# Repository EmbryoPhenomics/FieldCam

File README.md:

# FieldCam

## A submersible field camera and sensor instrument

FieldCam is a versatile, waterproof imaging and sensing instrument, powered by consumer AA batteries and capable of long term timelapse imaging out in the field.

 Some of the key specifications of this instrument are as follows:

| Component | Description |
|:---|:---|
| Waterproof enclosure | Acrylic tube with aluminium end caps rated to 130m depth |
| Battery | 17.1 Ah AA battery pack (~24 hrs continuous video recording). Capacity for additional 22.8 Ah AA battery pack (~30 hrs). Low power mode is > 10 years with continuous system and sensor monitoring (5 second resolution) |
| Processors | STM32 L4 microcontroller for system control and low power standby. Raspberry Pi Zero 2W for video and image capture, 32gb and 1Tb SD cards for storage respectively |
| Camera sensor | CMOS 12-megapixel (Sony IMX708) |
| Video resolution | 1080p50fps maximum. Resolution and framerate can be configured using built-in app |
| Focus | Phase Detection Autofocus (PDAF) or manual adjustable focus. Range 5cm to > 2m. | 
| Camera parameters | Exposure (Auto or manual), analogue gain and auto-white balance modes can all be configured via Web App |
| Lighting | Built-in adjustable LEDs (x2) with up to 170 lm each |
| Sensors | Temperature and light built-in. Pressure, salinity, pH and O2 available with additional sensor pack | 
| Configuration | Setup via Web App using smartphone or laptop, connected to the instrument’s wifi hotspot. Web App enables live streaming and config of camera sensor, viewing of system status and programming of experimental schedule.  All data, including video and sensor logs can be downloaded via network file sharing when in setup mode | 
| Dimensions | 70 mm x 195 mm |

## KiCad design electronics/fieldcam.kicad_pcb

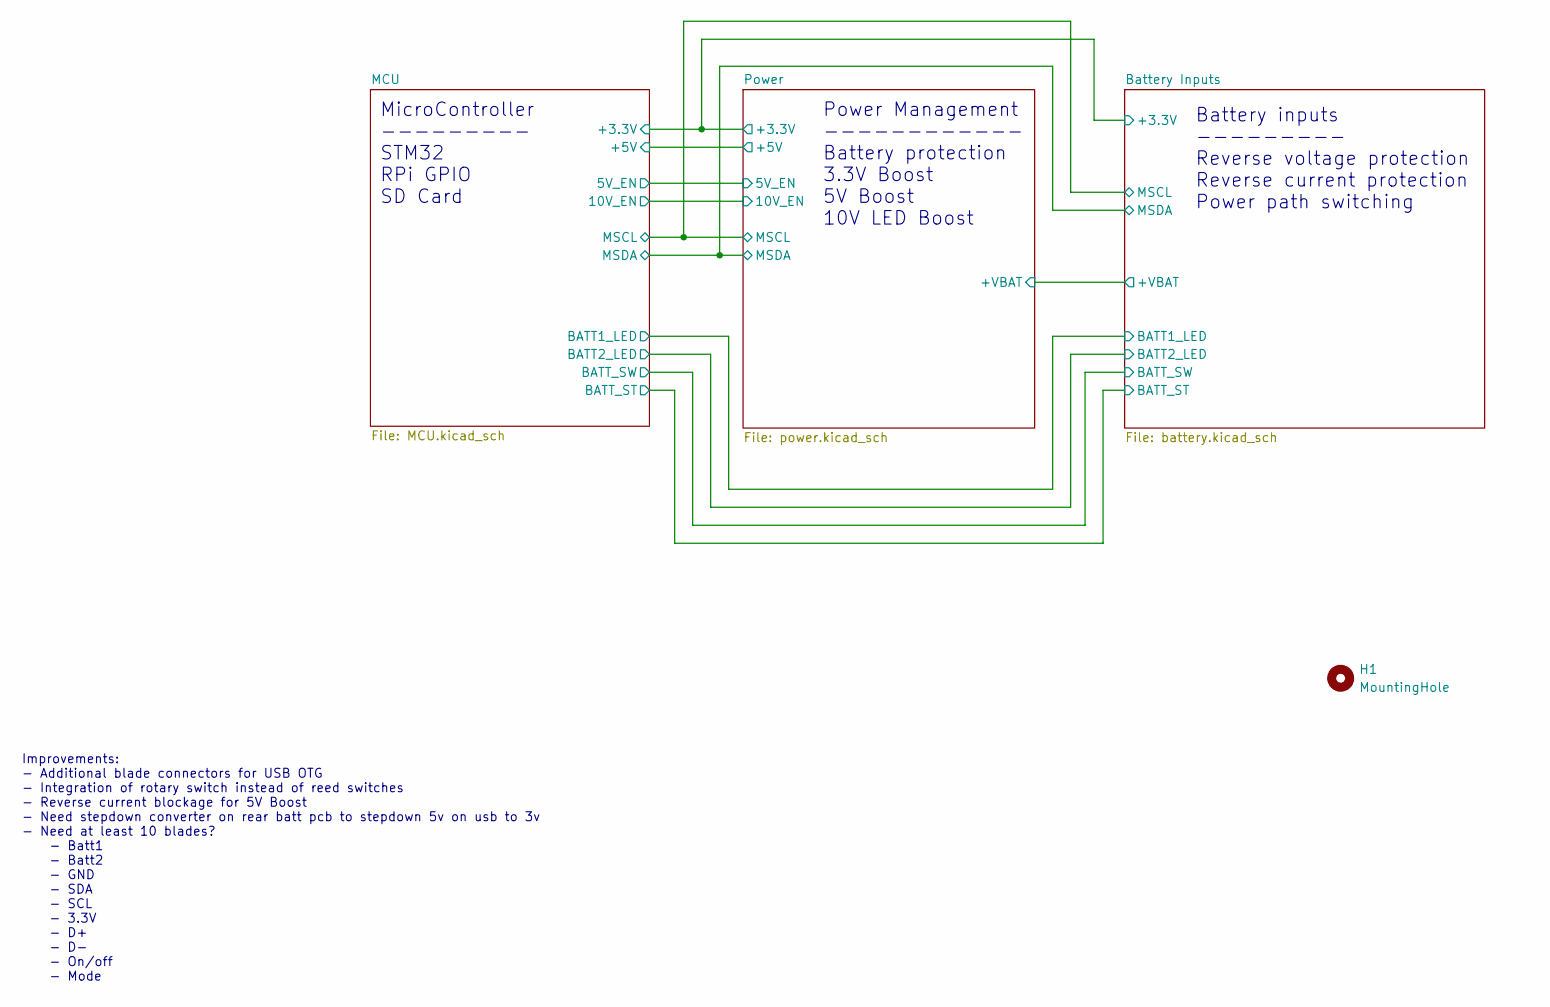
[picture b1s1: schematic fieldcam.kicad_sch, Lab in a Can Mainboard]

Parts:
H1: MountingHole; MountingHole_2.7mm_M2.5

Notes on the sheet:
Improvements: - Additional blade connectors for USB OTG - Integration of rotary switch instead of reed switches - Reverse current blockage for 5V Boost - Need stepdown converter on rear batt pcb to stepdown 5v on usb to 3v - Need at least 10 blades? - Batt1 - Batt2 - GND - SDA - SCL - 3.3V - D+ - D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
Power Management ------------ Battery protection 3.3V Boost 5V Boost 10V LED Boost
Battery inputs --------- Reverse voltage protection Reverse current protection Power path switching
MicroController --------- STM32 RPi GPIO SD Card

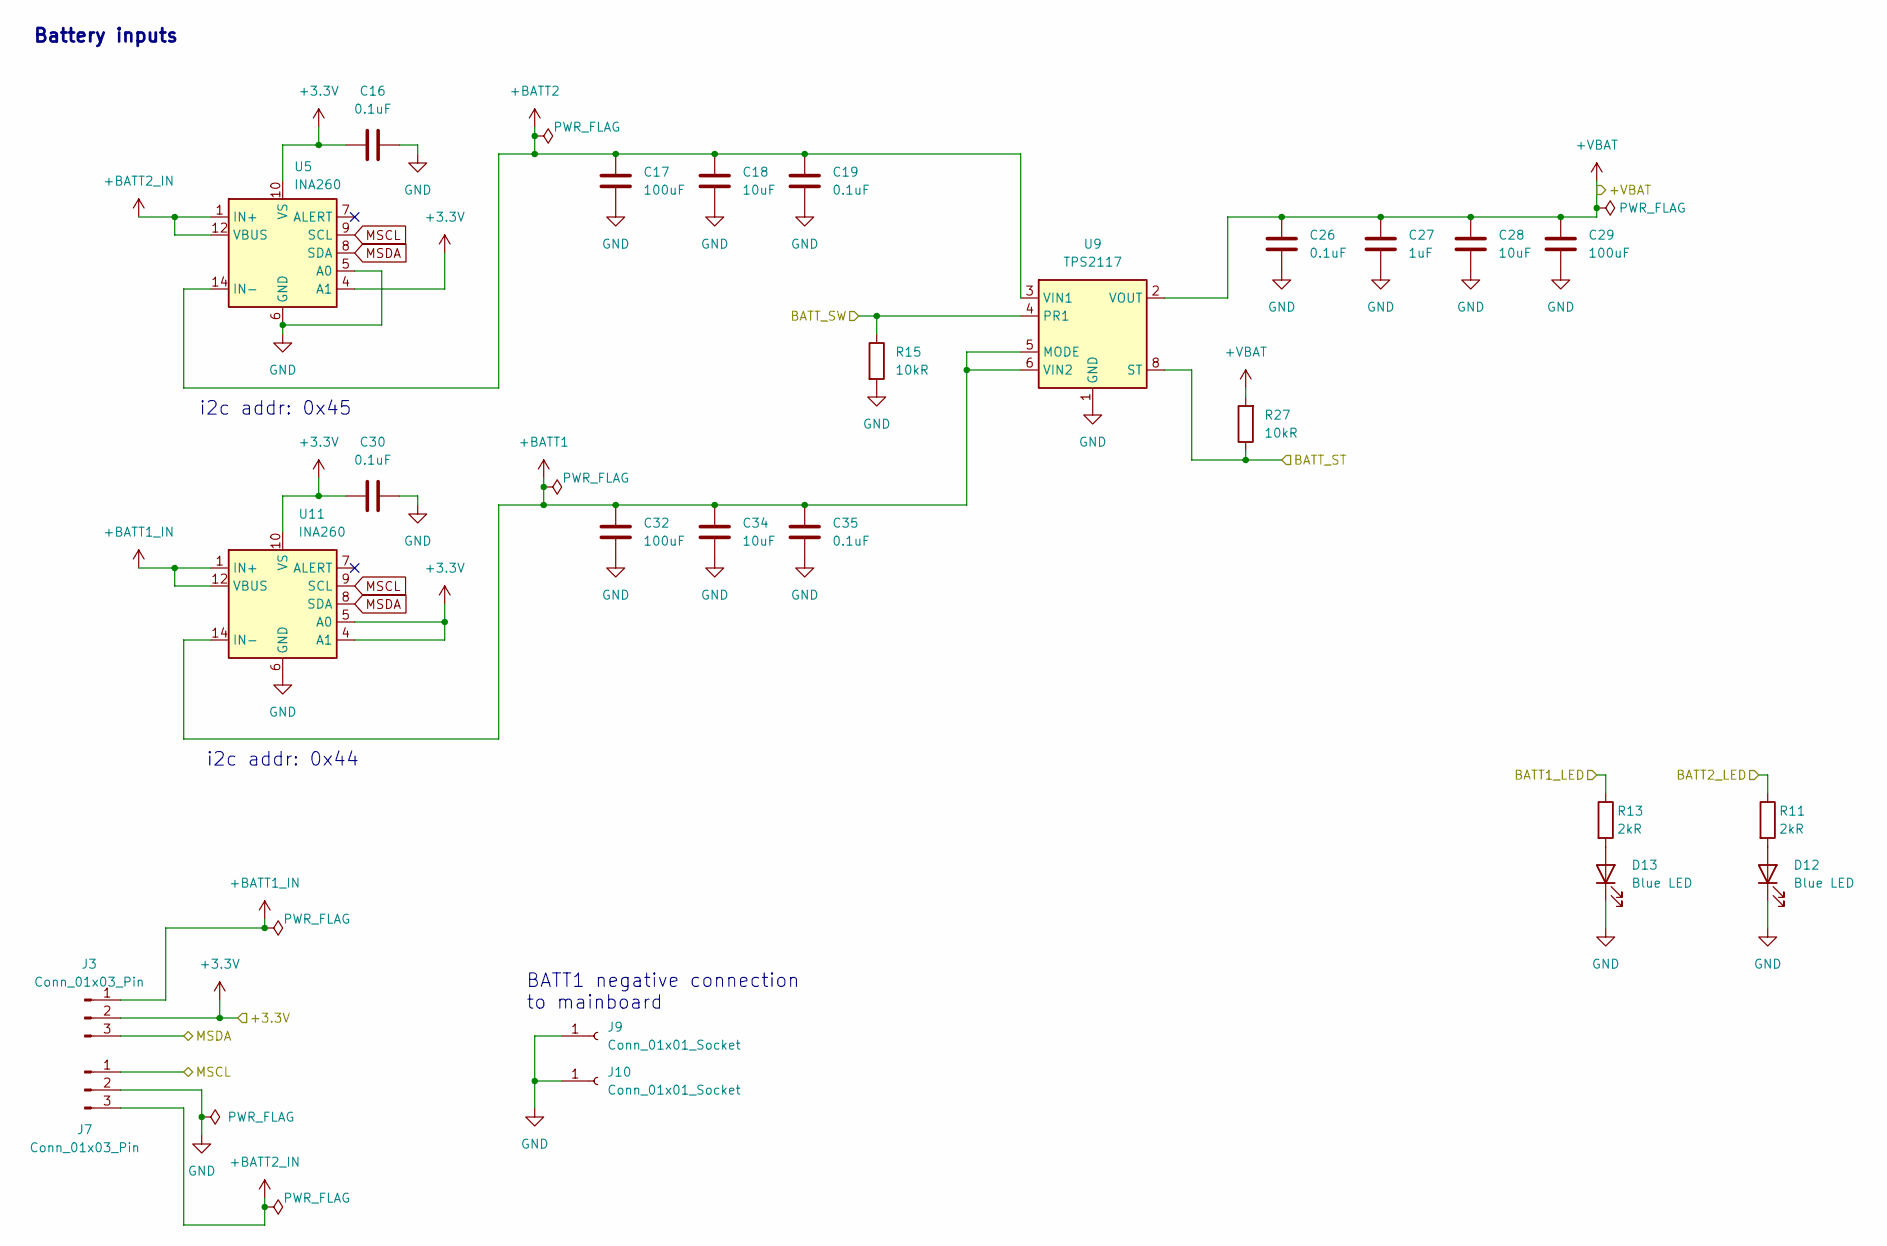
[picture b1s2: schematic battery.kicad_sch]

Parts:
C16, C19, C26, C30, C35: 0.1uF; C_0603_1608Metric
C17, C29, C32: 100uF; C_1210_3225Metric
C18, C28, C34: 10uF; C_0805_2012Metric
C27: 1uF; C_0603_1608Metric
D12, D13: Blue LED; LED_0603_1608Metric
J3, J7: Conn_01x03_Pin; 16129011
J9, J10: Conn_01x01_Socket; TestPoint_Pad_2.0x2.0mm
R11, R13: 2kR; R_0603_1608Metric
R15, R27: 10kR; R_0603_1608Metric
U5, U11: INA260; TSSOP-16_4.4x5mm_P0.65mm
U9: TPS2117; SOT-583-8

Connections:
+3.3V: C16.1, C30.1, J3.2, U5.4 (A1), U5.10 (VS), U11.4 (A1), U11.5 (A0), U11.10 (VS); also elsewhere on the board
+BATT1: C32.1, C34.1, C35.1, U9.5 (MODE), U9.6 (VIN2), U11.14 (IN-), U11.15 (IN-), U11.16 (IN-)
+BATT1_IN: J3.1, U11.1 (IN+), U11.2 (IN+), U11.3 (IN+), U11.12 (VBUS)
+BATT2: C17.1, C18.1, C19.1, U5.14 (IN-), U5.15 (IN-), U5.16 (IN-), U9.3 (VIN1)
+BATT2_IN: J7.3, U5.1 (IN+), U5.2 (IN+), U5.3 (IN+), U5.12 (VBUS)
+VBAT: C26.1, C27.1, C28.1, C29.1, R27.2, U9.2 (VOUT), U9.7 (VOUT); also elsewhere on the board
/Battery Inputs/BATT1_LED: R13.1; also elsewhere on the board
/Battery Inputs/BATT2_LED: R11.1; also elsewhere on the board
/Battery Inputs/BATT_ST: R27.1, U9.8 (ST); also elsewhere on the board
/Battery Inputs/BATT_SW: R15.1, U9.4 (PR1); also elsewhere on the board
GND: C16.2, C17.2, C18.2, C19.2, C26.2, C27.2, C28.2, C29.2, C30.2, C32.2, C34.2, C35.2, D12.1 (K), D13.1 (K), J7.2, J9.1 (Pin_1_1), J10.1 (Pin_1_1), R15.2, U5.5 (A0), U5.6 (GND), U5.11 (GND), U9.1 (GND), U11.6 (GND), U11.11 (GND); also elsewhere on the board
MSCL: J7.1, U5.9 (SCL), U11.9 (SCL); also elsewhere on the board
MSDA: J3.3, U5.8 (SDA), U11.8 (SDA); also elsewhere on the board
unnamed: D12.2 (A), R11.2
unnamed: D13.2 (A), R13.2

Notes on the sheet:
i2c addr: 0x45
BATT1 negative connection to mainboard
Battery inputs
i2c addr: 0x44

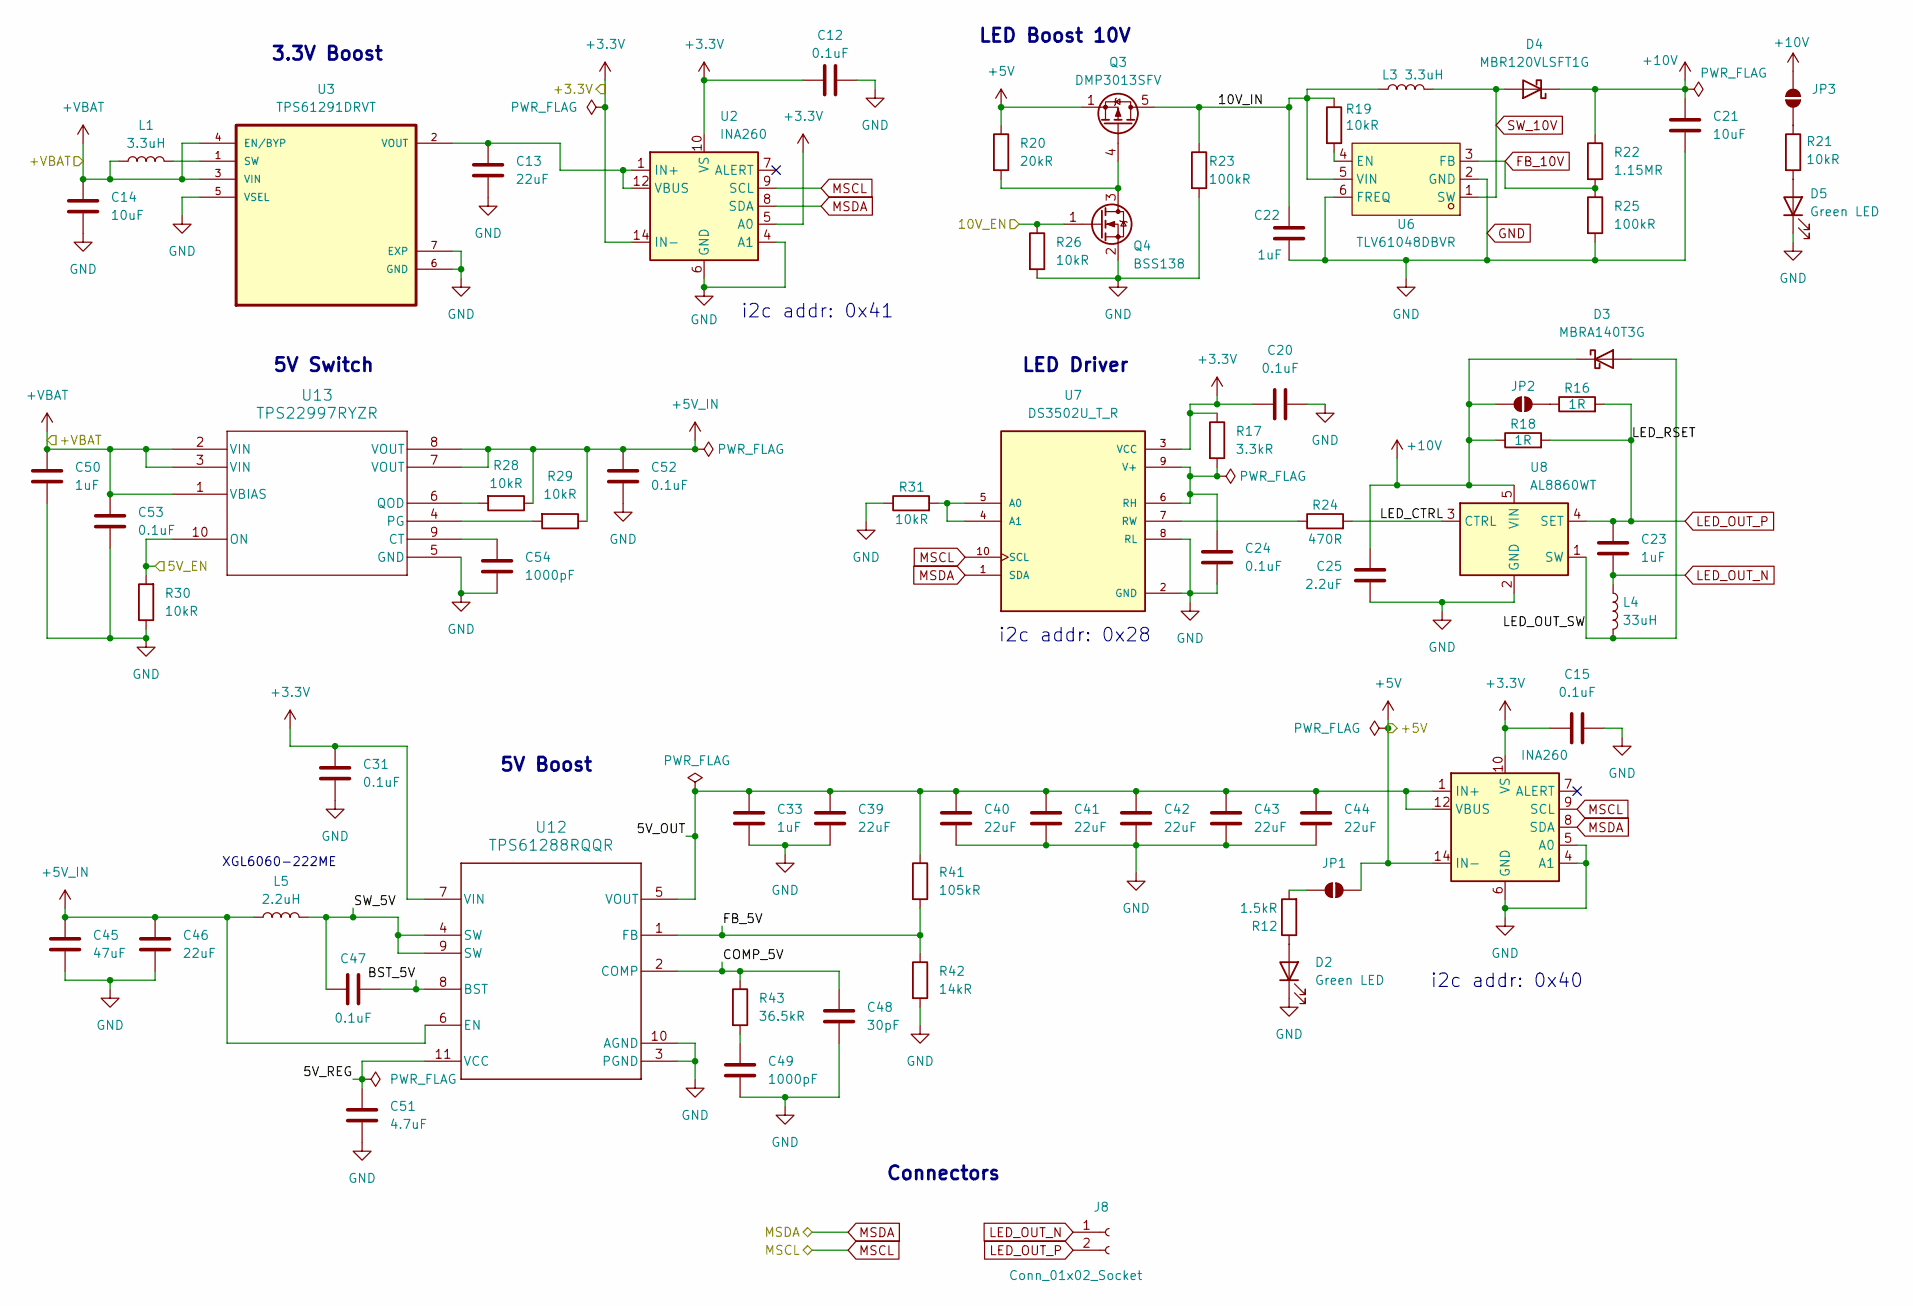
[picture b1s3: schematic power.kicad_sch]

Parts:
C12, C15, C20, C24, C47, C52, C53: 0.1uF; C_0603_1608Metric
C13: 22uF; C_0805_2012Metric
C14, C21: 10uF; C_0805_2012Metric
C22, C33: 1uF; C_0603_1608Metric
C23, C50: 1uF; C_0805_2012Metric
C25: 2.2uF; C_0805_2012Metric
C31: 0.1uF; C_0402_1005Metric
C39, C40, C41, C42, C43, C44, C46: 22uF; C_1206_3216Metric
C45: 47uF; C_1206_3216Metric
C48: 30pF; C_0402_1005Metric
C49, C54: 1000pF; C_0402_1005Metric
C51: 4.7uF; C_0603_1608Metric
D2, D5: Green LED; LED_0603_1608Metric
D3: MBRA140T3G; SMA_L4.3-W2.6-LS5.2-RD
D4: MBR120VLSFT1G
J8: Conn_01x02_Socket; JST_PH_S2B-PH-K_1x02_P2.00mm_Horizontal
JP1, JP2, JP3: SolderJumper_2_Open; SolderJumper-2_P1.3mm_Open_Pad1.0x1.5mm
L1, L3: 3.3uH; L_Coilcraft_XAL4030-XXX
L4: 33uH; L_Bourns_SRP7028A_7.3x6.6mm
L5: 2.2uH; L_Coilcraft_XAL6060-XXX
Q3: DMP3013SFV; Diodes_PowerDI3333-8
Q4: BSS138; SOT-23
R12: 1.5kR; R_0603_1608Metric
R16, R18: 1R; R_1206_3216Metric
R17: 3.3kR; R_0603_1608Metric
R19, R21, R26, R28, R29, R30, R31: 10kR; R_0603_1608Metric
R20: 20kR; R_0603_1608Metric
R22: 1.15MR; R_0603_1608Metric
R23, R25: 100kR; R_0603_1608Metric
R24: 470R; R_0603_1608Metric
R41: 105kR; R_0402_1005Metric
R42: 14kR; R_0402_1005Metric
R43: 36.5kR; R_0402_1005Metric
U2, U4: INA260; TSSOP-16_4.4x5mm_P0.65mm
U3: TPS61291DRVT; TPS61291
U6: TLV61048DBVR; SOT-23-6_L2.9-W1.6-P0.95-LS2.8-BR; LCSC Part C2861467
U7: DS3502U_T_R; SOP50P490X110-10N; PARTREV 23/05/19
U8: AL8860WT; TSOT-23-5
U12: TPS61288RQQR; TPS61288_VQFN-HR-11_L3.0-W2.5-P0.50-TL
U13: TPS22997RYZR; WQFN-HR10_RYZ_TEX

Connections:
+3.3V: C12.1, C15.1, C20.1, C31.1, R17.1, U2.5 (A0), U2.10 (VS), U2.14 (IN-), U2.15 (IN-), U2.16 (IN-), U4.10 (VS), U7.3 (VCC), U12.7 (VIN); also elsewhere on the board
+5V: JP1.1 (A), Q3.1 (S), Q3.2 (S), Q3.3 (S), R20.1, U4.14 (IN-), U4.15 (IN-), U4.16 (IN-); also elsewhere on the board
+5V_IN: C45.1, C46.1, C52.1, L5.1, R28.1, R29.1, U12.6 (EN), U13.7 (VOUT), U13.8 (VOUT)
+10V: C21.1, C25.1, D3.1 (K), D4.1 (K), JP2.2 (B), JP3.2 (B), R18.1, R22.1, U8.5 (VIN)
+VBAT: C14.1, C50.1, C53.1, L1.1, U3.3 (VIN), U3.4 (EN/BYP), U13.1 (VBIAS), U13.2 (VIN), U13.3 (VIN); also elsewhere on the board
/MCU/5V_EN: R30.2, U13.10 (ON); also elsewhere on the board
/MCU/10V_EN: Q4.1 (G), R26.1; also elsewhere on the board
/Power/5V_OUT: C33.1, C39.1, C40.1, C41.1, C42.1, C43.1, C44.1, R41.1, U4.1 (IN+), U4.2 (IN+), U4.3 (IN+), U4.12 (VBUS), U12.5 (VOUT)
/Power/5V_REG: C51.1, U12.11 (VCC)
/Power/10V_IN: C22.1, L3.1, Q3.5 (D), R19.1, R23.1, U6.5 (VIN)
/Power/BST_5V: C47.2, U12.8 (BST)
/Power/COMP_5V: C48.1, R43.1, U12.2 (COMP)
/Power/FB_5V: R41.2, R42.1, U12.1 (FB)
/Power/LED_CTRL: R24.2, U8.3 (CTRL)
/Power/LED_OUT_SW: D3.2 (A), L4.2, U8.1 (SW)
/Power/SW_5V: C47.1, L5.2, U12.4 (SW), U12.9 (SW)
FB_10V: R22.2, R25.1, U6.3 (FB)
GND: C12.2, C13.2, C14.2, C15.2, C20.2, C21.2, C22.2, C24.1, C25.2, C31.2, C33.2, C39.2, C40.2, C41.2, C42.2, C43.2, C44.2, C45.2, C46.2, C48.2, C49.2, C50.2, C51.2, C52.2, C53.2, C54.2, D2.1 (K), D5.1 (K), Q4.2 (S), R23.2, R25.2, R26.2, R30.1, R31.1, R42.2, U2.4 (A1), U2.6 (GND), U2.11 (GND), U3.5 (VSEL), U3.6 (GND), U3.7 (EXP), U4.4 (A1), U4.5 (A0), U4.6 (GND), U4.11 (GND), U6.2 (GND), U6.6 (FREQ), U7.2 (GND), U7.8 (RL), U8.2 (GND), U12.3 (PGND), U12.10 (AGND), U13.5 (GND); also elsewhere on the board
LED_OUT_N: C23.2, J8.1, L4.1
LED_OUT_P: C23.1, J8.2, R16.2, R18.2, U8.4 (SET)
MSCL: U2.9 (SCL), U4.9 (SCL), U7.10 (SCL); also elsewhere on the board
MSDA: U2.8 (SDA), U4.8 (SDA), U7.1 (SDA); also elsewhere on the board
unnamed: C49.1, R43.2
unnamed: D2.2 (A), R12.1
unnamed: D5.2 (A), R21.2
unnamed: JP1.2 (B), R12.2
unnamed: JP2.1 (A), R16.1
unnamed: JP3.1 (A), R21.1
unnamed: Q3.4 (G), Q4.3 (D), R20.2
unnamed: C13.1, U2.1 (IN+), U2.2 (IN+), U2.3 (IN+), U2.12 (VBUS), U3.2 (VOUT)
unnamed: L1.2, U3.1 (SW)
unnamed: R19.2, U6.4 (EN)
unnamed: R31.2, U7.4 (A1), U7.5 (A0)
unnamed: C24.2, R17.2, U7.6 (RH), U7.9 (V+)
unnamed: R24.1, U7.7 (RW)
unnamed: C54.1, U13.9 (CT)
unnamed: R29.2, U13.4 (PG)
unnamed: R28.2, U13.6 (QOD)
SW_10V: D4.2 (A), L3.2, U6.1 (SW)

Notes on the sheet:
5V Switch
i2c addr: 0x28
i2c addr: 0x41
LED Driver
LED Boost 10V
i2c addr: 0x40
XGL6060-222ME
Connectors
3.3V Boost
5V Boost

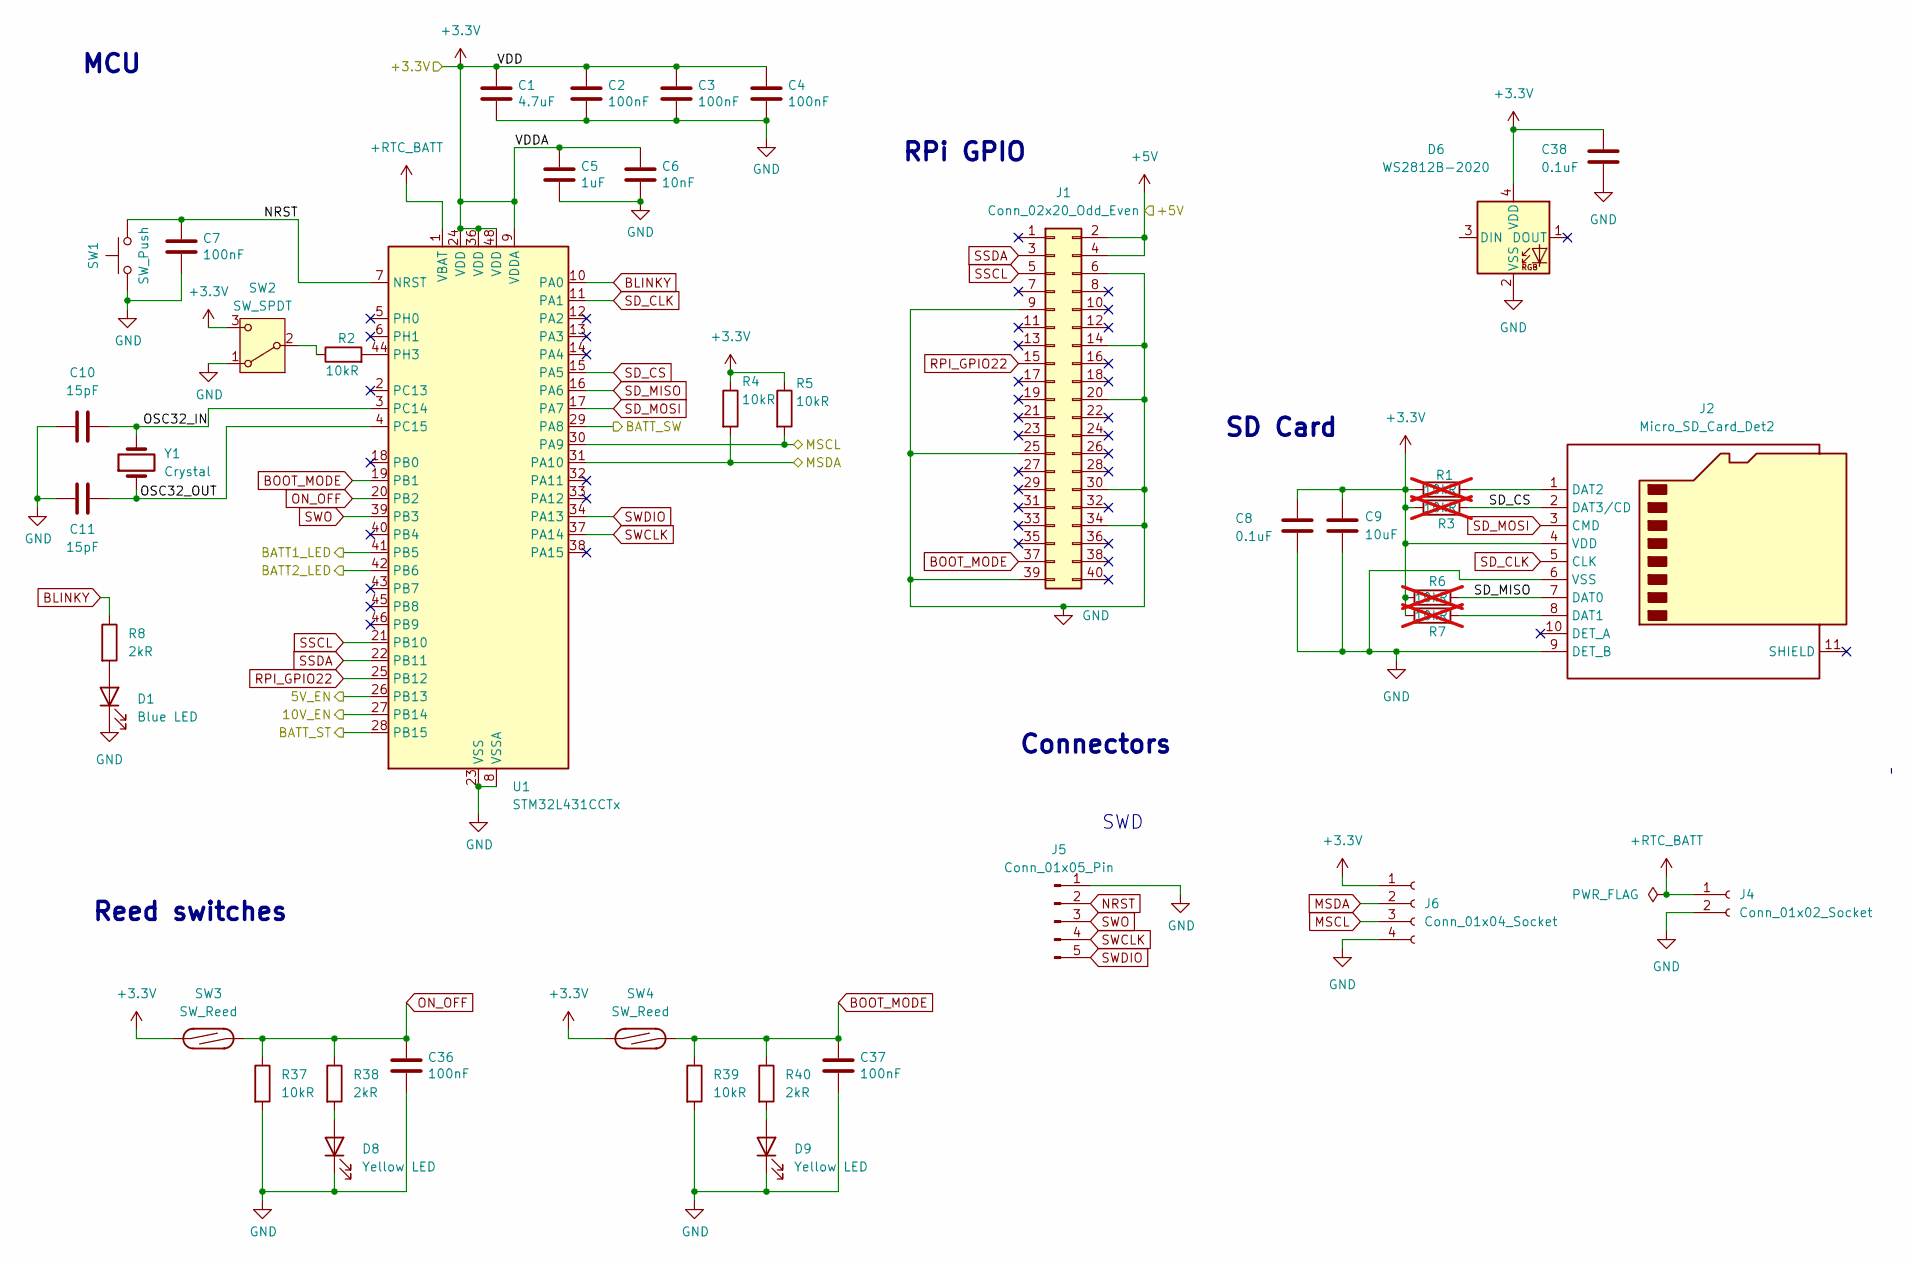
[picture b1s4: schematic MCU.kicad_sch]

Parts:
C1: 4.7uF; C_0603_1608Metric
C2, C3, C4, C7, C36, C37: 100nF; C_0402_1005Metric
C5: 1uF; C_0603_1608Metric
C6: 10nF; C_0402_1005Metric
C8, C38: 0.1uF; C_0402_1005Metric
C9: 10uF; C_0603_1608Metric
C10, C11: 15pF; C_0402_1005Metric
D1: Blue LED; LED_0603_1608Metric
D6: WS2812B-2020; LED_WS2812B-2020_PLCC4_2.0x2.0mm
D8, D9: Yellow LED; LED_0603_1608Metric
J1: Conn_02x20_Odd_Even; CONN-SMD_FH-00369_2x40
J2: Micro_SD_Card_Det2; microSD_HC_Molex_104031-0811
J4: Conn_01x02_Socket; JST_SH_SM02B-SRSS-TB_1x02-1MP_P1.00mm_Horizontal
J5: Conn_01x05_Pin; JST_SH_BM05B-SRSS-TB_1x05-1MP_P1.00mm_Vertical
J6: Conn_01x04_Socket; JST_SH_SM04B-SRSS-TB_1x04-1MP_P1.00mm_Horizontal
R1, R3, R6, R7: 10kR; R_0402_1005Metric; not fitted
R2, R4, R5: 10kR; R_0402_1005Metric
R8, R38, R40: 2kR; R_0603_1608Metric
R37, R39: 10kR; R_0603_1608Metric
SW1: SW_Push; SW-SMD_L3.9-W3.0-P4.45
SW2: SW_SPDT; SW-SMD_MSK12CO2
SW3, SW4: SW_Reed; SENSOR-SMD_59170-1-S-00-D
U1: STM32L431CCTx; LQFP-48_7x7mm_P0.5mm
Y1: Crystal; FC-135R_L3.2-W1.5

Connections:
+3.3V: C1.1, C2.1, C3.1, C4.1, C5.1, C6.1, C8.1, C9.1, C38.1, D6.4 (VDD), J2.4 (VDD), J6.1, R1.1, R3.1, R4.1, R5.1, R6.1, R7.1, SW2.3 (C), SW3.1, SW4.1, U1.9 (VDDA), U1.24 (VDD), U1.36 (VDD), U1.48 (VDD); also elsewhere on the board
+5V: J1.2, J1.4; also elsewhere on the board
+RTC_BATT: J4.1, U1.1 (VBAT)
/Battery Inputs/BATT1_LED: U1.41 (PB5); also elsewhere on the board
/Battery Inputs/BATT2_LED: U1.42 (PB6); also elsewhere on the board
/Battery Inputs/BATT_ST: U1.28 (PB15); also elsewhere on the board
/Battery Inputs/BATT_SW: U1.29 (PA8); also elsewhere on the board
/MCU/5V_EN: U1.26 (PB13); also elsewhere on the board
/MCU/10V_EN: U1.27 (PB14); also elsewhere on the board
/MCU/OSC32_IN: C10.2, U1.3 (PC14), Y1.2
/MCU/OSC32_OUT: C11.2, U1.4 (PC15), Y1.1
BLINKY: R8.1, U1.10 (PA0)
BOOT_MODE: C37.1, J1.37, R39.1, R40.1, SW4.2, U1.19 (PB1)
GND: C1.2, C2.2, C3.2, C4.2, C5.2, C6.2, C7.2, C8.2, C9.2, C10.1, C11.1, C36.2, C37.2, C38.2, D1.1 (K), D6.2 (VSS), D8.1 (K), D9.1 (K), J1.6, J1.9, J1.14, J1.20, J1.25, J1.30, J1.34, J1.39, J2.6 (VSS), J2.9 (DET_B), J4.2, J5.1, J6.4, R37.2, R39.2, SW1.1, SW2.1 (A), U1.8 (VSSA), U1.23 (VSS), U1.35 (VSS), U1.47 (VSS); also elsewhere on the board
MSCL: J6.3, R5.2, U1.30 (PA9); also elsewhere on the board
MSDA: J6.2, R4.2, U1.31 (PA10); also elsewhere on the board
NRST: C7.1, J5.2, SW1.2, U1.7 (NRST)
unnamed: D1.2 (A), R8.2
unnamed: D8.2 (A), R38.2
unnamed: D9.2 (A), R40.2
unnamed: J2.8 (DAT1), R7.2
unnamed: J2.1 (DAT2), R1.2
unnamed: R2.1, SW2.2 (B)
unnamed: R2.2, U1.44 (PH3)
ON_OFF: C36.1, R37.1, R38.1, SW3.2, U1.20 (PB2)
RPI_GPIO22: J1.15, U1.25 (PB12)
SD_CLK: J2.5 (CLK), U1.11 (PA1)
SD_CS: J2.2 (DAT3/CD), R3.2, U1.15 (PA5)
SD_MISO: J2.7 (DAT0), R6.2, U1.16 (PA6)
SD_MOSI: J2.3 (CMD), U1.17 (PA7)
SSCL: J1.5, U1.21 (PB10)
SSDA: J1.3, U1.22 (PB11)
SWCLK: J5.4, U1.37 (PA14)
SWDIO: J5.5, U1.34 (PA13)
SWO: J5.3, U1.39 (PB3)

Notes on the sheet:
Connectors
SWD
MCU
RPi GPIO
Reed switches
SD Card

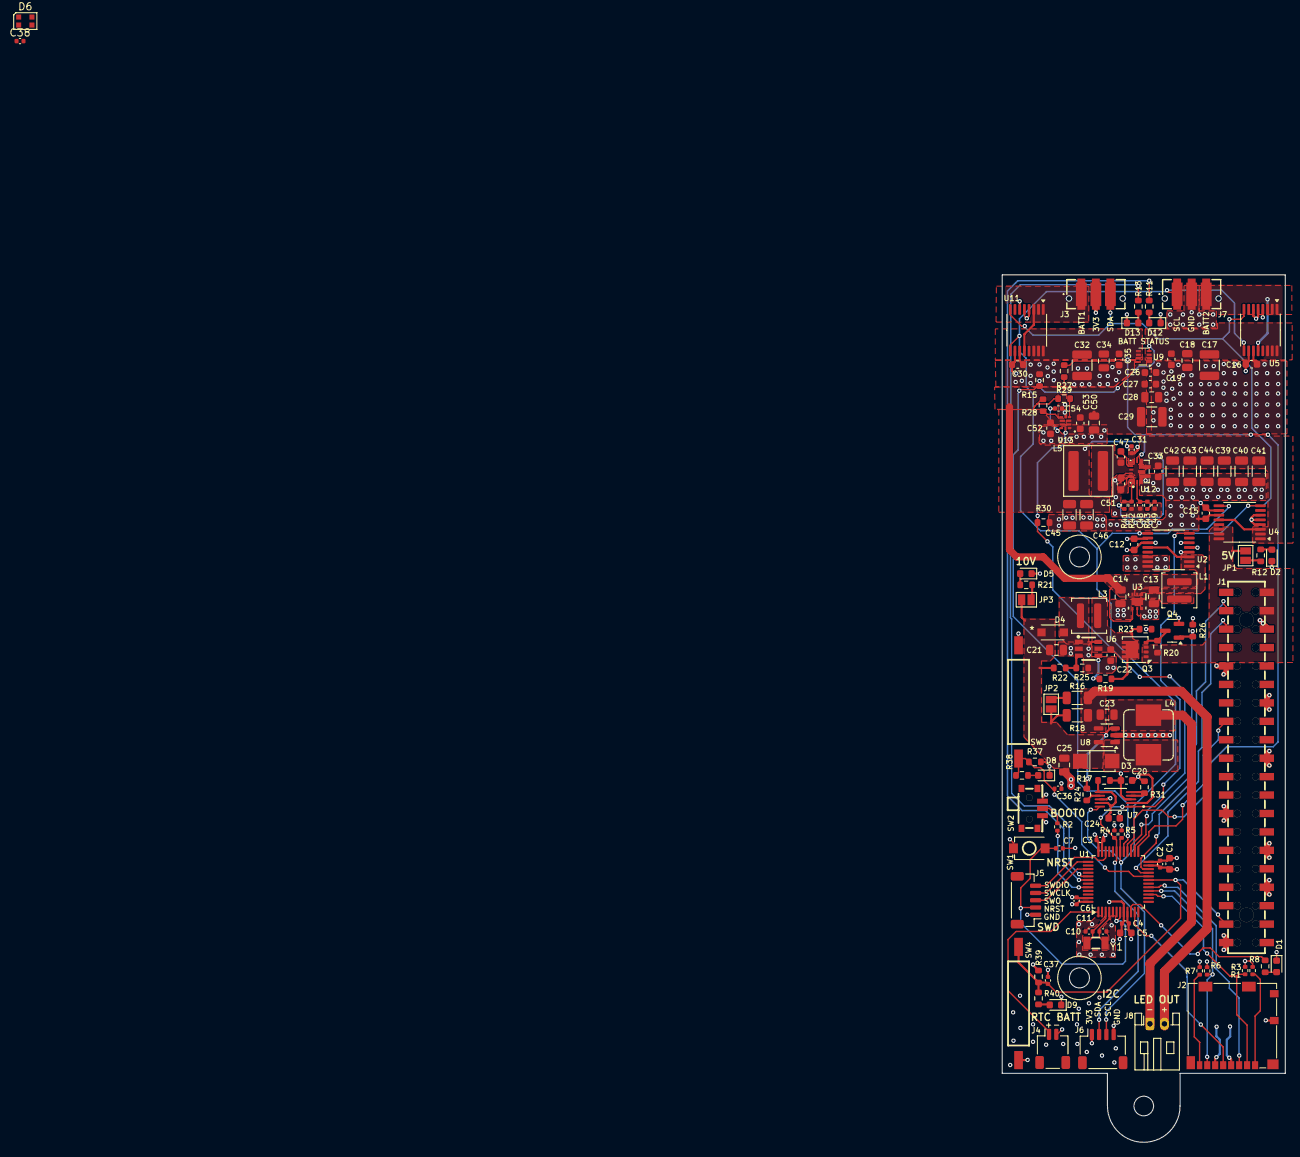
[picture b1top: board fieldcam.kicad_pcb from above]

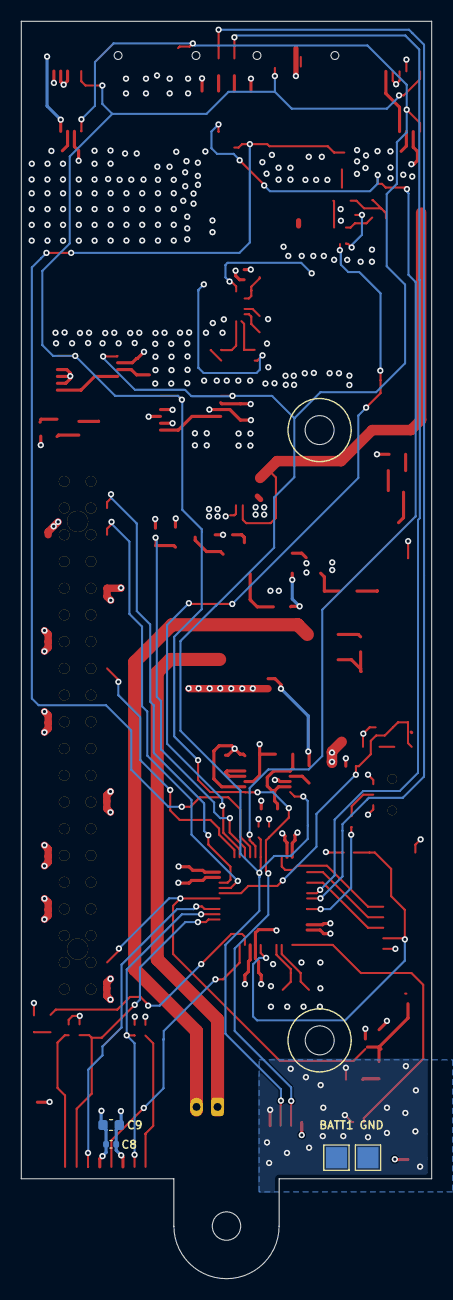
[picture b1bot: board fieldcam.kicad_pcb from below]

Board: 4 copper layers, 39.0 x 119.5 mm, 136 parts (4 on the bottom side), 73 nets.

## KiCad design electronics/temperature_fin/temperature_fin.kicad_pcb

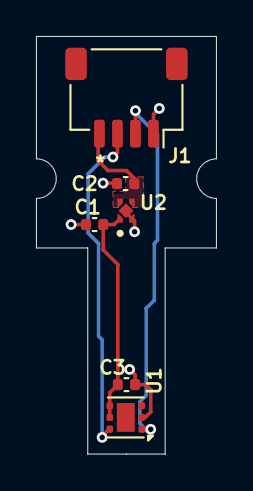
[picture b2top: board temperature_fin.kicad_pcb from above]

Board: 2 copper layers, 10.0 x 23.2 mm, 6 parts (0 on the bottom side), 5 nets.

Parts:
C1, C2: 1uF; C_0402_1005Metric
C3: 0.1uF; C_0402_1005Metric
J1: Conn_01x04_Socket; JST_SH_SM04B-SRSS-TB_1x04-1MP_P1.00mm_Horizontal
U1: TMP117xxDRV; WSON-6-1EP_2x2mm_P0.65mm_EP1x1.6mm
U2: TPS7A0228PDQNR; IC_TPS7A0228PDQNR

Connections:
+2V8: C1.1, C3.1, U1.4 (ADD0), U1.5 (V+), U2.1 (OUT)
+3V3: C2.1, J1.4, U2.3 (EN), U2.4 (IN)
GND: C1.2, C2.2, C3.2, J1.1, U1.2 (GND), U2.2 (GND), U2.5 (THERMAL_PAD)
SCL: J1.2, U1.1 (SCL)
SDA: J1.3, U1.6 (SDA)

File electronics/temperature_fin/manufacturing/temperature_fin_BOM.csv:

"Reference","Qty","Value","DNP","Exclude from BOM","Exclude from Board","Footprint","Datasheet"
"C1,C2","2","1uF","","","","Capacitor_SMD:C_0402_1005Metric","~"
"C3","1","0.1uF","","","","Capacitor_SMD:C_0402_1005Metric","~"
"J1","1","Conn_01x04_Socket","","","","Connector_JST:JST_SH_SM04B-SRSS-TB_1x04-1MP_P1.00mm_Horizontal","~"
"U1","1","TMP117xxDRV","","","","Package_SON:WSON-6-1EP_2x2mm_P0.65mm_EP1x1.6mm","https://www.ti.com/lit/ds/symlink/tmp117.pdf"
"U2","1","TPS7A0228PDQNR","","","","jlcpcb:IC_TPS7A0228PDQNR",""

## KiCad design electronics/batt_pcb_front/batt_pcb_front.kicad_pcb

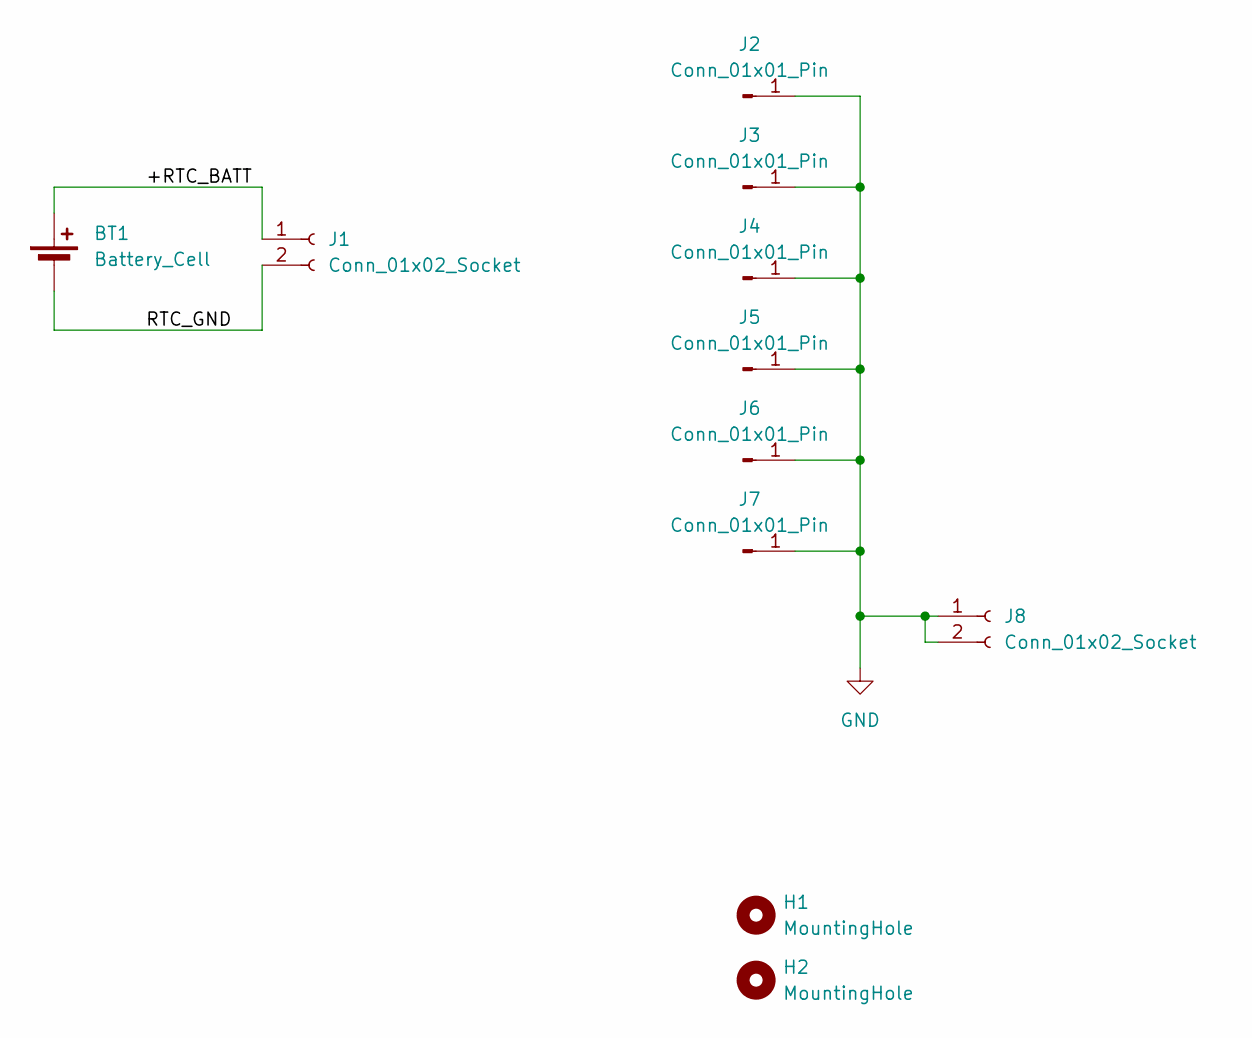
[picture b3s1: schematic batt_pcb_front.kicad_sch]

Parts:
BT1: Battery_Cell; BatteryHolder_Keystone_3000_1x12mm
H1, H2: MountingHole; MountingHole_2.7mm_M2.5
J1: Conn_01x02_Socket; JST_SH_BM02B-SRSS-TB_1x02-1MP_P1.00mm_Vertical
J2, J3, J4, J5, J6, J7: Conn_01x01_Pin; TestPoint_Pad_D4.0mm
J8: Conn_01x02_Socket; JST_PH_S2B-PH-SM4-TB_1x02-1MP_P2.00mm_Horizontal

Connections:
/+RTC_BATT: BT1.1 (+), J1.1
/RTC_GND: BT1.2 (-), J1.2
GND: J2.1, J3.1, J4.1, J5.1, J6.1, J7.1, J8.1, J8.2

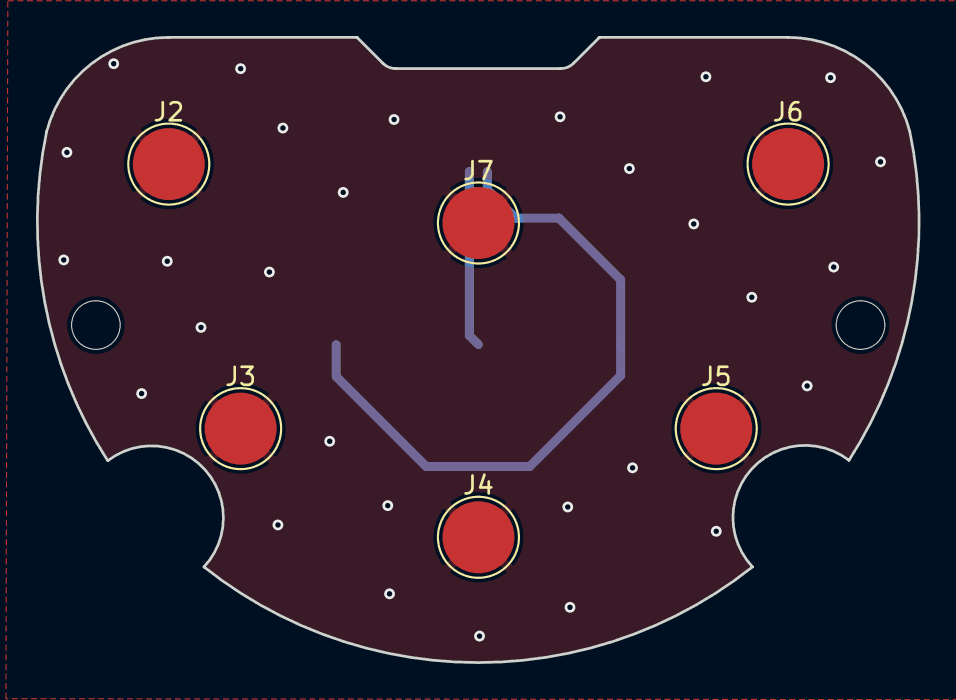
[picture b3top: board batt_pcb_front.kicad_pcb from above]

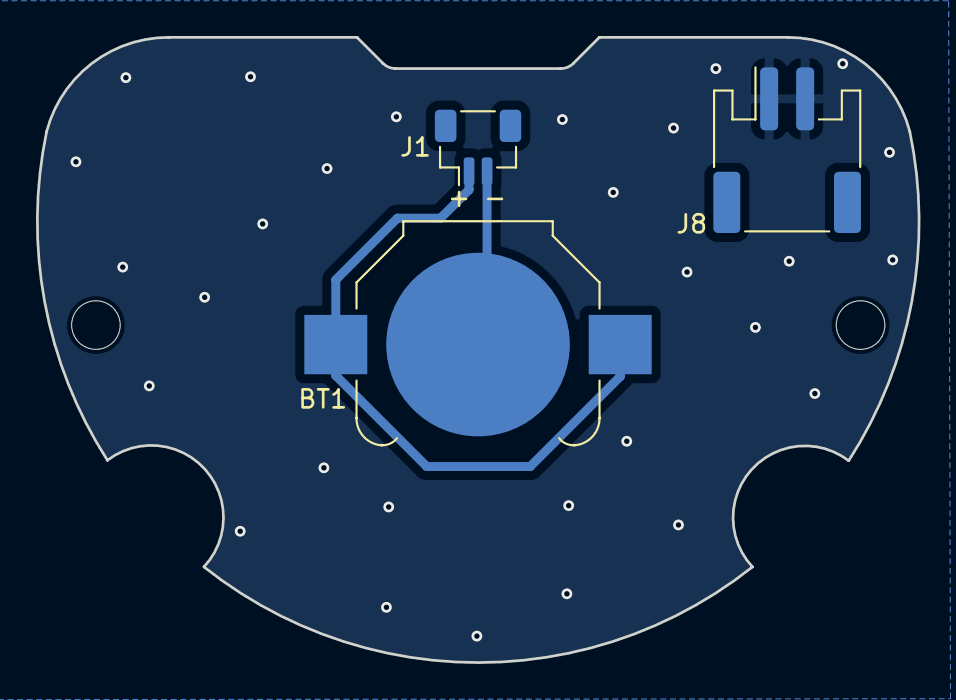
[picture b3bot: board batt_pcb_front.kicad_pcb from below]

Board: 2 copper layers, 49.0 x 34.7 mm, 11 parts (3 on the bottom side), 3 nets.

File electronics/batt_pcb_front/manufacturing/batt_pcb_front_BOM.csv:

"Reference","Qty","Value","DNP","Exclude from BOM","Exclude from Board","Footprint","Datasheet"
"BT1","1","Battery_Cell","","","","Battery:BatteryHolder_Keystone_3000_1x12mm","~"
"J1","1","Conn_01x02_Socket","","","","Connector_JST:JST_SH_BM02B-SRSS-TB_1x02-1MP_P1.00mm_Vertical","~"
"J2,J3,J4,J5,J6,J7","6","Conn_01x01_Pin","","","","jlcpcb:HARWIN_S7091-42R","~"
"J8","1","Conn_01x02_Socket","","","","Connector_JST:JST_PH_S2B-PH-SM4-TB_1x02-1MP_P2.00mm_Horizontal","~"
